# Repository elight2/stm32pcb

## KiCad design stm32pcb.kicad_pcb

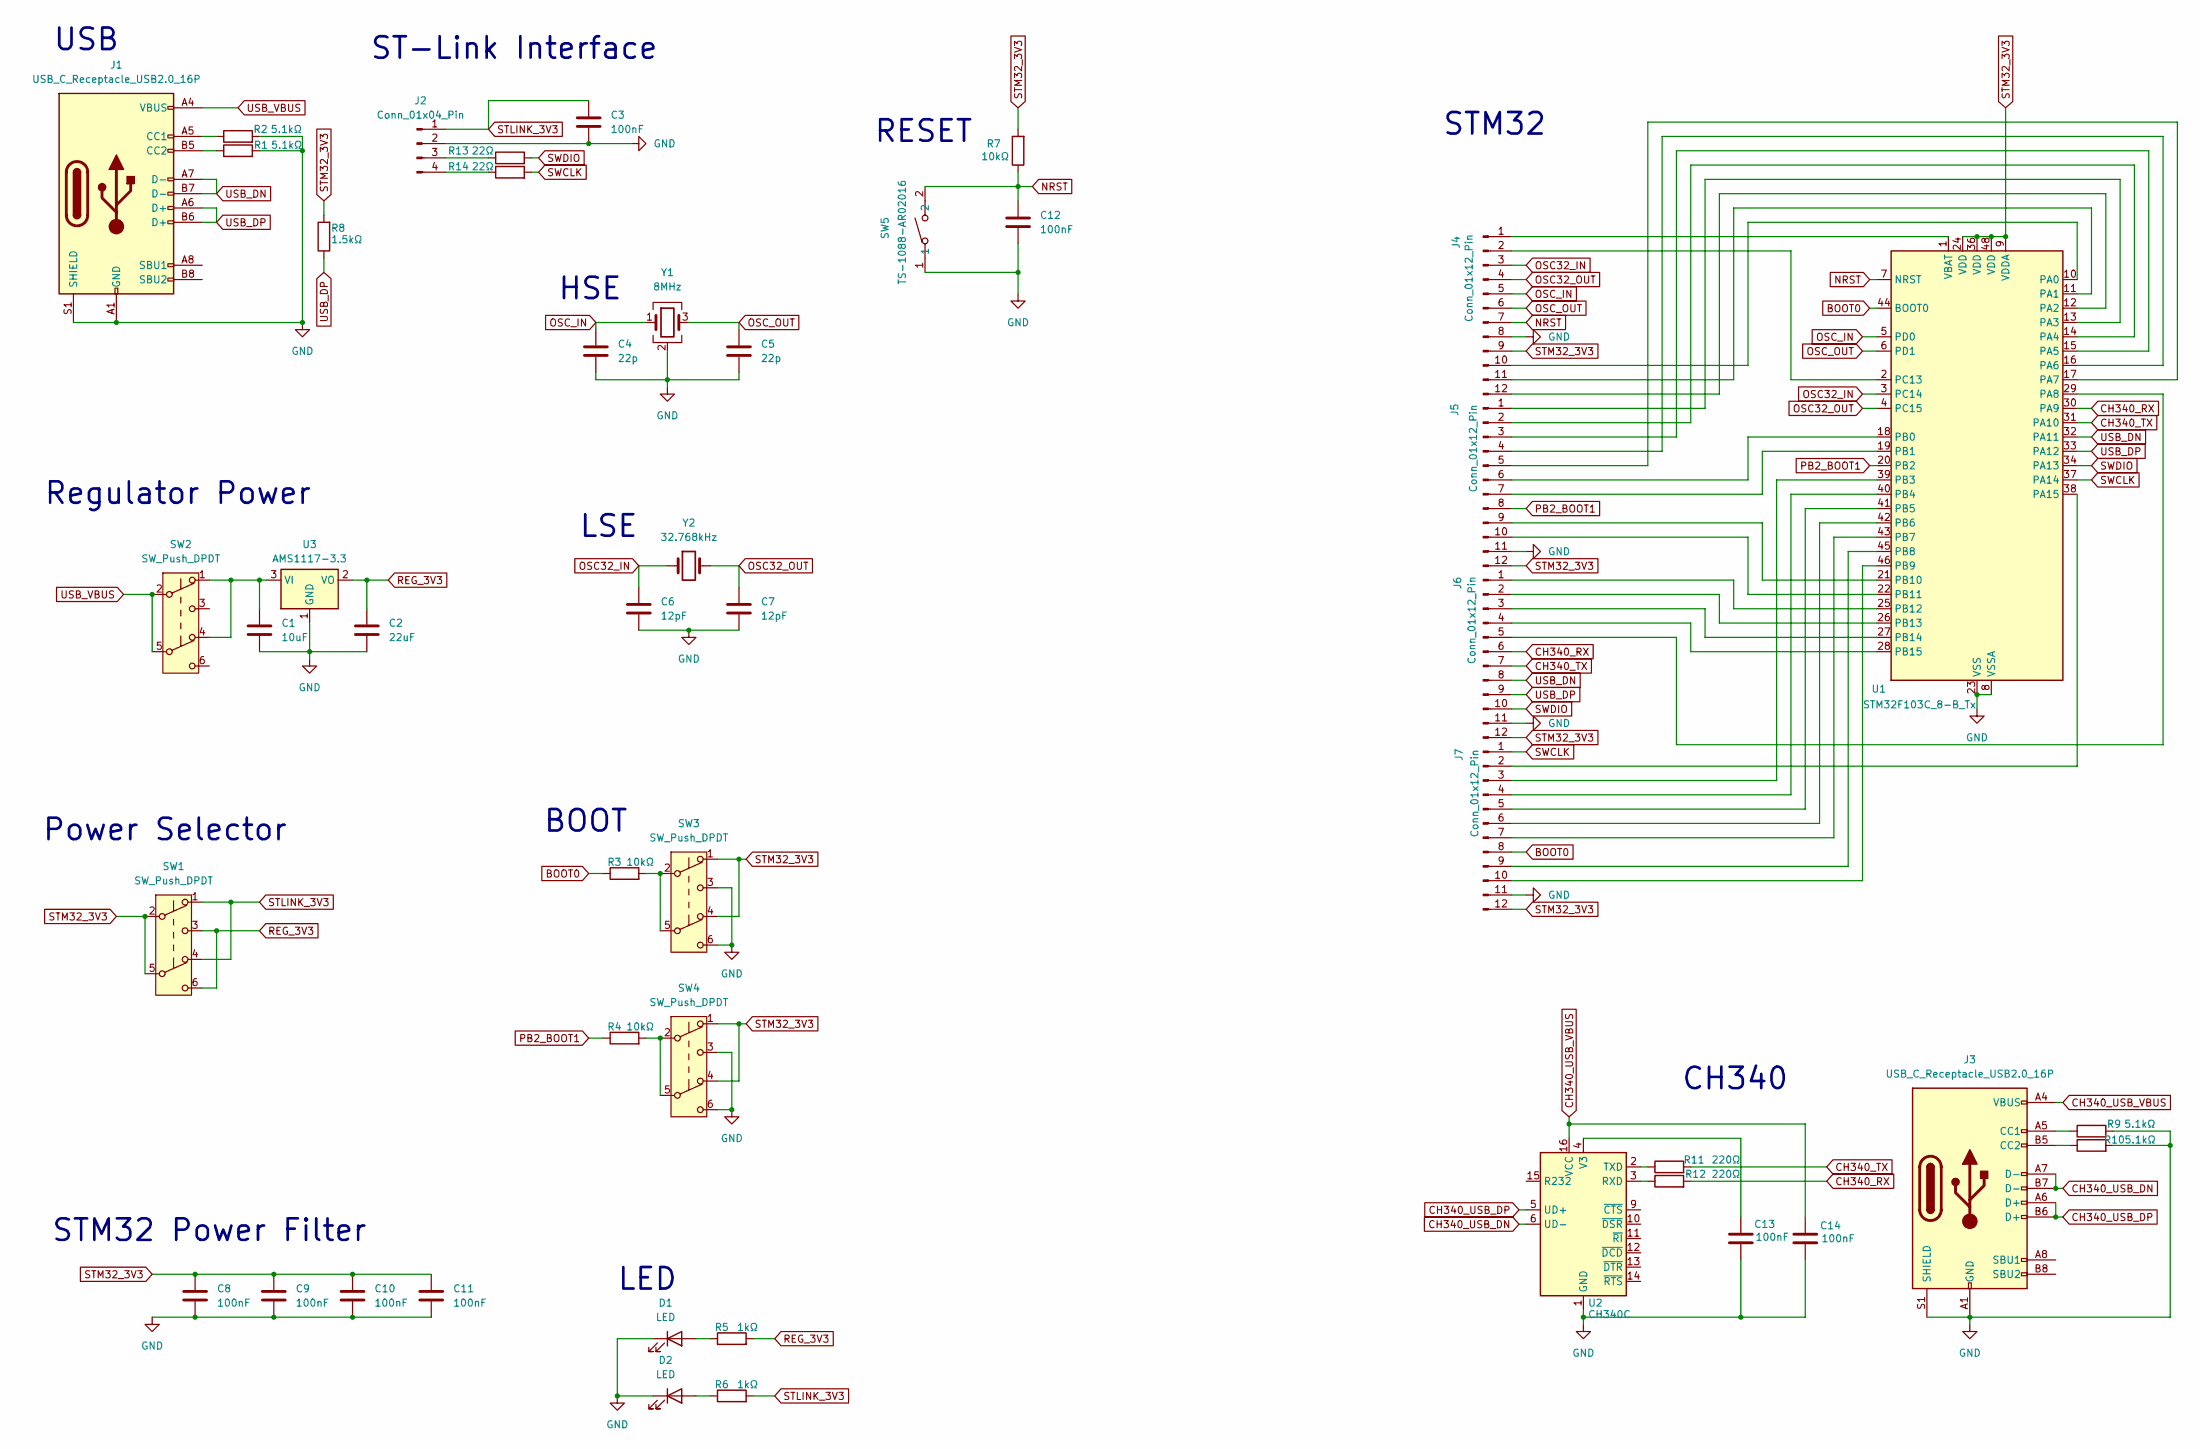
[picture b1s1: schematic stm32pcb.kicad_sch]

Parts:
C1: 10uF; C_0805_2012Metric
C2: 22uF; C_0805_2012Metric
C3, C8, C9, C10, C11, C12, C13, C14: 100nF; C_0805_2012Metric
C4, C5: 22p; C_0805_2012Metric
C6, C7: 12pF; C_0805_2012Metric
D1, D2: LED; LED_0805_2012Metric
J1, J3: USB_C_Receptacle_USB2.0_16P; USB-C-SMD_HH-16P-CB-TYPE-C
J2: Conn_01x04_Pin; PinHeader_1x04_P2.54mm_Horizontal
J4, J5, J6, J7: Conn_01x12_Pin; PinHeader_1x12_P2.54mm_Vertical
R1, R2, R9, R10: 5.1kΩ; R_1206_3216Metric
R3, R4, R7: 10kΩ; R_1206_3216Metric
R5, R6: 1kΩ; R_1206_3216Metric
R8: 1.5kΩ; R_1206_3216Metric
R11, R12: 220Ω; R_1206_3216Metric
R13, R14: 22Ω; R_1206_3216Metric
SW1, SW2, SW3, SW4: SW_Push_DPDT; SW-SMD_6P-L9.1-W3.5-P2.50
SW5: TS-1088-AR02016; SW-SMD_L3.9-W3.0-P4.45; LCSC Part C720477
U1: STM32F103C_8-B_Tx; LQFP-48_7x7mm_P0.5mm
U2: CH340C; SOIC-16_3.9x9.9mm_P1.27mm
U3: AMS1117-3.3; SOT-223-3_TabPin2
Y1: 8MHz; Crystal_SMD_3225-4Pin_3.2x2.5mm
Y2: 32.768kHz; Crystal_SMD_3215-2Pin_3.2x1.5mm

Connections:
BOOT0: J7.8, R3.1, U1.44 (BOOT0)
CH340_RX: J6.6, R12.2, U1.30 (PA9)
CH340_TX: J6.7, R11.2, U1.31 (PA10)
CH340_USB_DN: J3.A7 (D-), J3.B7 (D-), U2.6 (UD-)
CH340_USB_DP: J3.A6 (D+), J3.B6 (D+), U2.5 (UD+)
CH340_USB_VBUS: C14.1, J3.A4 (VBUS), J3.A9 (VBUS), J3.B4 (VBUS), J3.B9 (VBUS), U2.16 (VCC)
GND: C1.2, C2.2, C3.2, C4.2, C5.2, C6.2, C7.2, C8.2, C9.2, C10.2, C11.2, C12.2, C13.2, C14.2, D1.1 (K), D2.1 (K), J1.A1 (GND), J1.A12 (GND), J1.B1 (GND), J1.B12 (GND), J1.S1 (SHIELD), J2.2, J3.A1 (GND), J3.A12 (GND), J3.B1 (GND), J3.B12 (GND), J3.S1 (SHIELD), J4.8, J5.11, J6.11, J7.11, R1.2, R2.2, R9.2, R10.2, SW3.3 (C), SW3.6 (C), SW4.3 (C), SW4.6 (C), SW5.1, U1.8 (VSSA), U1.23 (VSS), U1.35 (VSS), U1.47 (VSS), U2.1 (GND), U3.1 (GND), Y1.2 (G), Y1.4 (G)
NRST: C12.1, J4.7, R7.1, SW5.2, U1.7 (NRST)
unnamed: D1.2 (A), R5.1
unnamed: D2.2 (A), R6.1
unnamed: J1.A5 (CC1), R2.1
unnamed: J1.B5 (CC2), R1.1
unnamed: J2.3, R13.1
unnamed: J2.4, R14.1
unnamed: J3.A5 (CC1), R9.1
unnamed: J3.B5 (CC2), R10.1
unnamed: J4.1, U1.1 (VBAT)
unnamed: J4.2, U1.2 (PC13)
unnamed: J4.10, U1.10 (PA0)
unnamed: J4.11, U1.11 (PA1)
unnamed: J4.12, U1.12 (PA2)
unnamed: J5.1, U1.13 (PA3)
unnamed: J5.2, U1.14 (PA4)
unnamed: J5.3, U1.15 (PA5)
unnamed: J5.4, U1.16 (PA6)
unnamed: J5.5, U1.17 (PA7)
unnamed: J5.6, U1.18 (PB0)
unnamed: J5.7, U1.19 (PB1)
unnamed: J5.9, U1.21 (PB10)
unnamed: J5.10, U1.22 (PB11)
unnamed: J6.1, U1.25 (PB12)
unnamed: J6.2, U1.26 (PB13)
unnamed: J6.3, U1.27 (PB14)
unnamed: J6.4, U1.28 (PB15)
unnamed: J6.5, U1.29 (PA8)
unnamed: J7.2, U1.38 (PA15)
unnamed: J7.3, U1.39 (PB3)
unnamed: J7.4, U1.40 (PB4)
unnamed: J7.5, U1.41 (PB5)
unnamed: J7.6, U1.42 (PB6)
unnamed: J7.7, U1.43 (PB7)
unnamed: J7.9, U1.45 (PB8)
unnamed: J7.10, U1.46 (PB9)
unnamed: R3.2, SW3.2 (B), SW3.5 (B)
unnamed: R4.2, SW4.2 (B), SW4.5 (B)
unnamed: R12.1, U2.3 (RXD)
unnamed: R11.1, U2.2 (TXD)
unnamed: C13.1, U2.4 (V3)
unnamed: C1.1, SW2.1 (A), SW2.4 (A), U3.3 (VI)
OSC32_IN: C6.1, J4.3, U1.3 (PC14), Y2.1
OSC32_OUT: C7.1, J4.4, U1.4 (PC15), Y2.2
OSC_IN: C4.1, J4.5, U1.5 (PD0), Y1.1
OSC_OUT: C5.1, J4.6, U1.6 (PD1), Y1.3
PB2_BOOT1: J5.8, R4.1, U1.20 (PB2)
REG_3V3: C2.1, R5.2, SW1.3 (C), SW1.6 (C), U3.2 (VO)
STLINK_3V3: C3.1, J2.1, R6.2, SW1.1 (A), SW1.4 (A)
STM32_3V3: C8.1, C9.1, C10.1, C11.1, J4.9, J5.12, J6.12, J7.12, R7.2, R8.2, SW1.2 (B), SW1.5 (B), SW3.1 (A), SW3.4 (A), SW4.1 (A), SW4.4 (A), U1.9 (VDDA), U1.24 (VDD), U1.36 (VDD), U1.48 (VDD)
SWCLK: J7.1, R14.2, U1.37 (PA14)
SWDIO: J6.10, R13.2, U1.34 (PA13)
USB_DN: J1.A7 (D-), J1.B7 (D-), J6.8, U1.32 (PA11)
USB_DP: J1.A6 (D+), J1.B6 (D+), J6.9, R8.1, U1.33 (PA12)
USB_VBUS: J1.A4 (VBUS), J1.A9 (VBUS), J1.B4 (VBUS), J1.B9 (VBUS), SW2.2 (B), SW2.5 (B)

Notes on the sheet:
LED
BOOT
LSE
RESET
STM32
Regulator Power
CH340
USB
ST-Link Interface
STM32 Power Filter
HSE
Power Selector

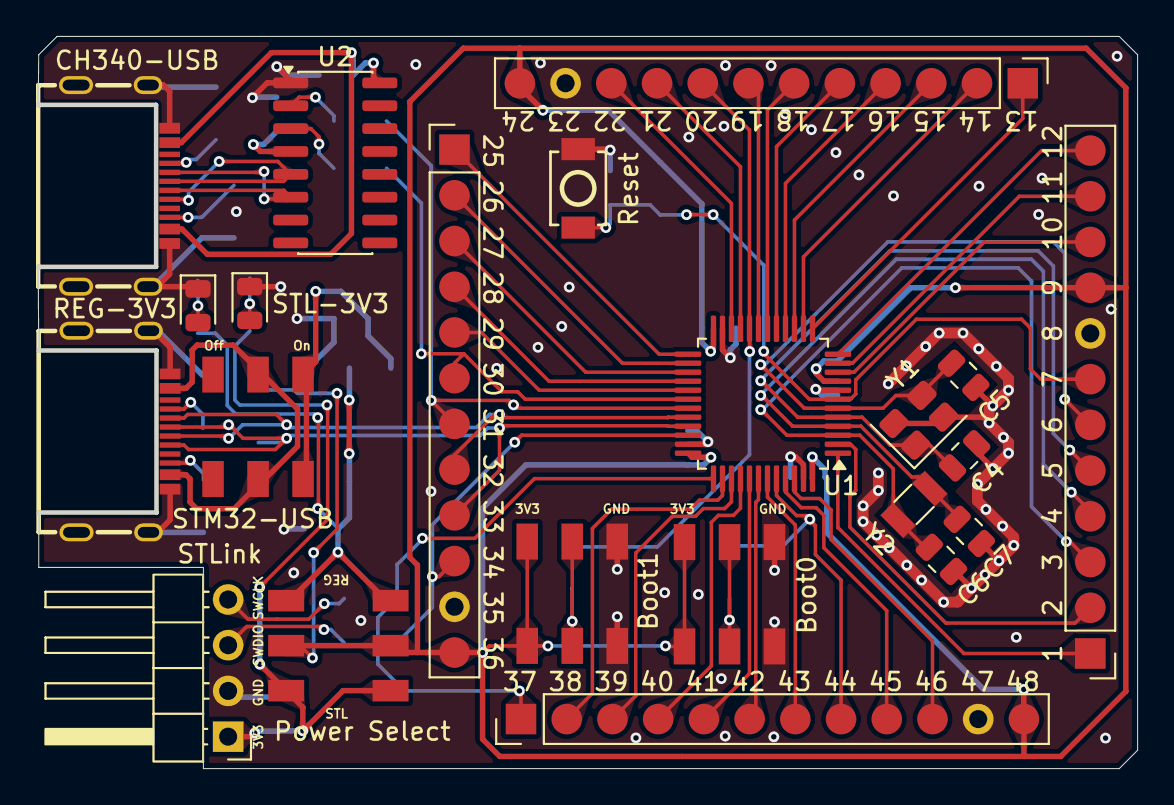
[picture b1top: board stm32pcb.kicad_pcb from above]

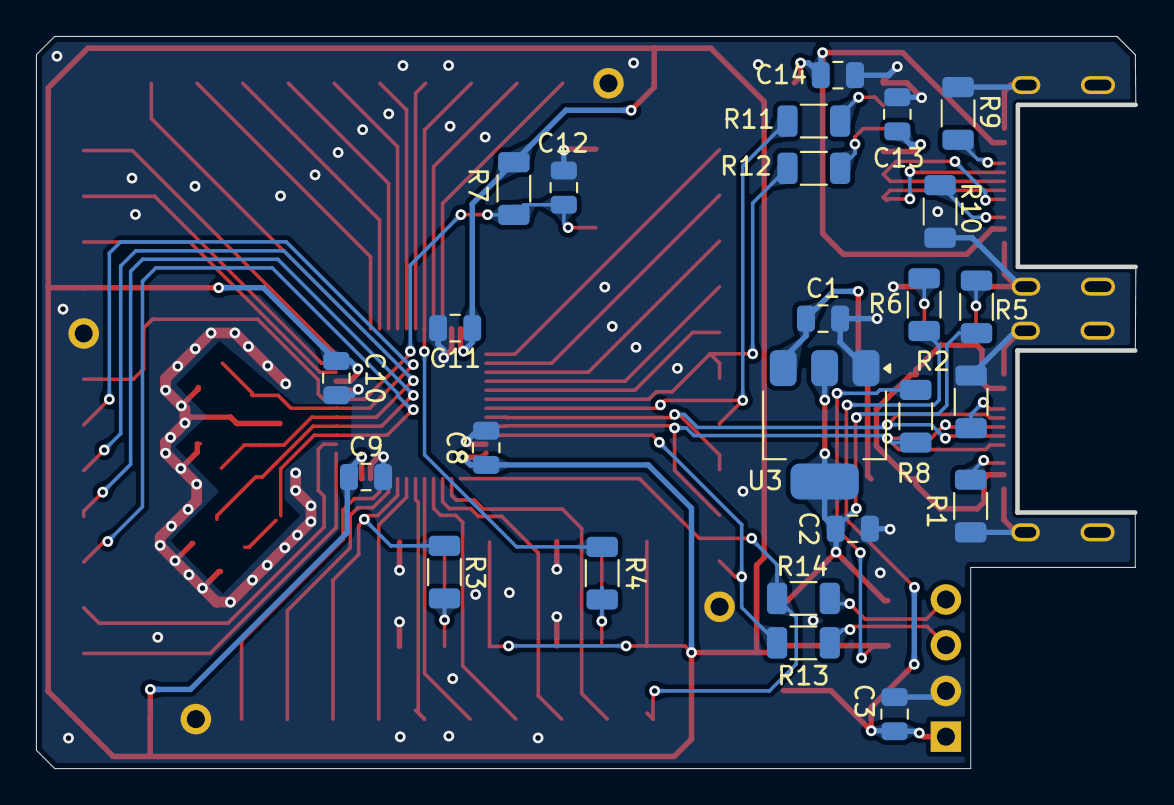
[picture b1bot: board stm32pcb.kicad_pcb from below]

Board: 2 copper layers, 61.0 x 40.5 mm, 47 parts (25 on the bottom side), 62 nets.
